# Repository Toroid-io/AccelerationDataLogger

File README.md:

# AccelerationDataLogger

**AccelerationDataLogger** provides a hardware-software bundle to
measure and log accelerations. Originally developed to measure
oscillations in engineering models, it may be used in the following
applications, among others:

 - Structural dynamics
 - Sports science
 - Simple vibration analysis
 - Fall detection
 - Wearables development
 - As an accelerometer playground

The board is capable of measuring **two accelerations simultaneously**
with a maximum sampling frequency of 800Hz, during 11 seconds. Longer
measurements are possible reducing the sampling rate, or using only one
accelerometer.

It currently uses jellybean parts as accelerometers. The board currently
supports the following breakout boards:
 - MPU6050 (GY-521 breakout)
 - ADXL345 (GY-291 and Sparkfun breakouts)

## Quick user manual
- Power the board using batteries or the USB cable.
- Fix the board into the structure or person.
- Calibrate the board by pressing the *Calibrate button*.
- Acquire the acceleration by pressing the *Acquire button*.
- Connect the board to your computer to download the data.

## The Hardware
You may find the KiCad schematic and board in the `Board` directory.

### Overview

The board does all the acquisition and storing procedure autonomously.
Hence, it may be battery powered during acquisition, and then connected
to a computer to download the data. In the current state, the board
requires at least 6.8V to work autonomously (this tension may be
provided by two LiPo cells or a 9V battery).

It has three pushable buttons, in order to reset the system, calibrate
the device and acquire data. A pushable switch enables or disables the
battery for autonomous mode.

The board may be connected to a computer using a USB micro-B cable.

That's all you need to know about the hardware!

### Memory

The board has 1MBit of RAM, where all the data is stored. Given that a
16-bit accelerometer provides 6 bytes of data for each measurement (plus
1 byte for the accelerometer ID), the board is capable of saving 18724
measurements.

That equals:
 - 11.7 seconds using two accelerometers at 800Hz
 - 23.4 seconds using one accelerometer at 800Hz
 - 6.24 minutes with one accelerometer at 50Hz
 - ...

## The Firmware

ChibiOS RTOS is used for the firmware. Tasks are used to separate the
acquisition of each sensor, write the RAM, and send measurements when
requested. Give a look into the `Firmware` folder.

## The acquisition software

A simple interface has been written in Qt C++, in order to download and
preview the data. The interface looks like this:

Currently, the interface only allows to connect and download the data
from the board. Future versions will allow the modification of some
parameters, such as the sampling frequency.

## I want one!

### Build One

You can build your own AccelerationDataLogger. Mounting the PCB requires
average soldering skills (0603 footprints and LQFP packages), but it is
the cheap way to go.

You can get the PCB from [OSH
Park](https://oshpark.com/shared_projects/0VAEaJ3K), or generate your
own Gerbers from the PCB. The BOM is in the `Board` directory.

### Get one built

We can send you a populated PCB. Just contact us at `admin [at]
toroid.io` for a quote.

## Development

### Contribute

Do you want to add or request a new feature? Did you find a bug in the
code? Create an issue or a pull request! All contributions are welcome.

### Future features

A non-exhaustive list of future features:
 - Add support to more accelerometers
 - Use a coin cell to power the system autonomously
 - Reduce the size of the board
 - Implement other MEMS features (DMP, fall detection)

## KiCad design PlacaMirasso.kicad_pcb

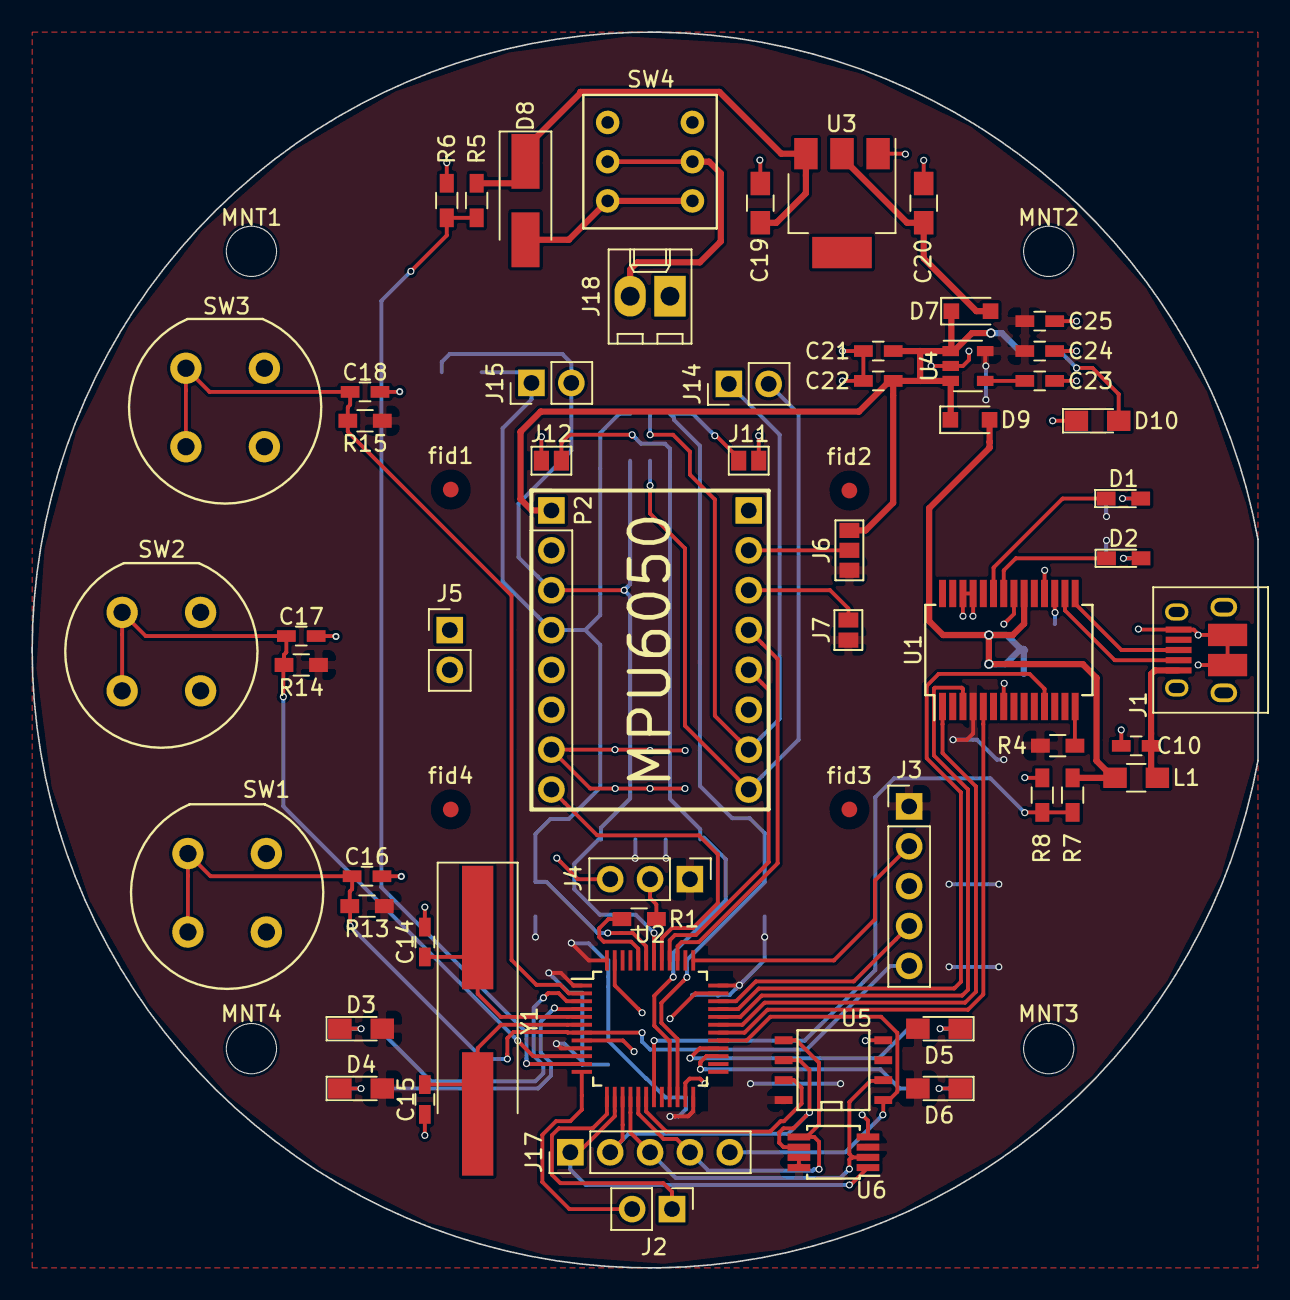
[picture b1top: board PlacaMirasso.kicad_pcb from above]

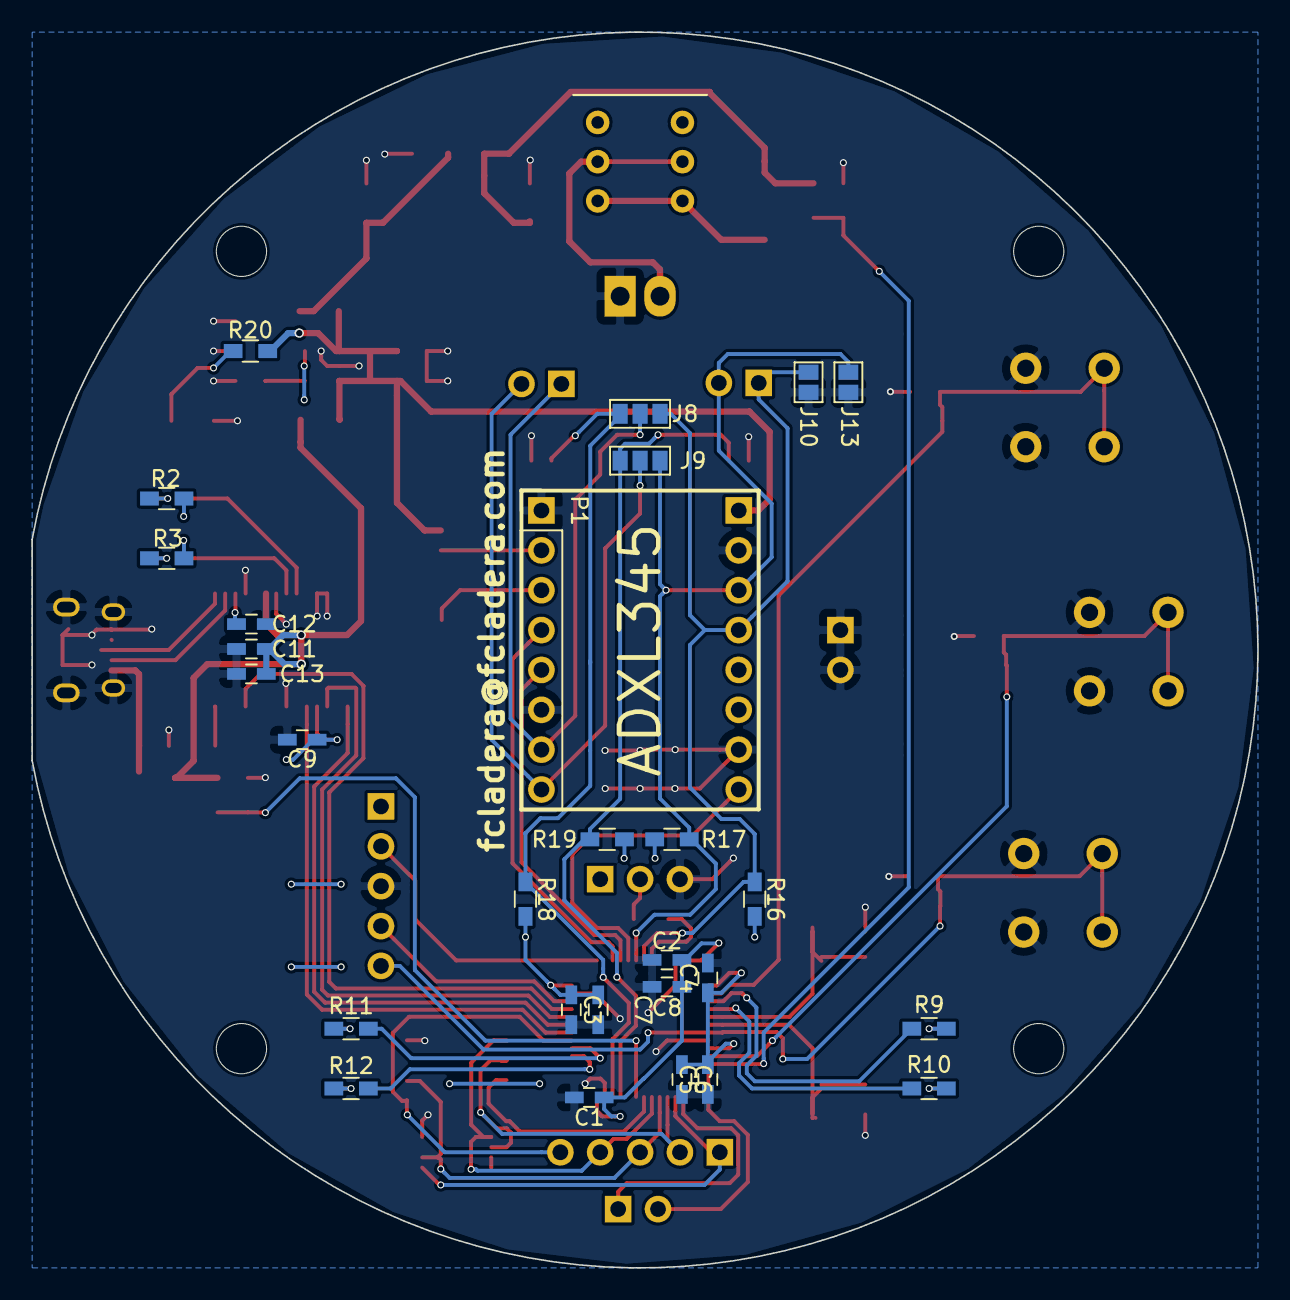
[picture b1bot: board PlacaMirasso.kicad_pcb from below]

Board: 2 copper layers, 78.1 x 78.7 mm, 94 parts (28 on the bottom side), 61 nets.

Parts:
C1, C2, C3, C4, C9, C11, C12, C16, C17, C18, C22, C25: 100nF; C_0603_HandSoldering
C5, C10, C23: 10nF_X7R; C_0603_HandSoldering
C6, C21, C24: 1uF_X5R; C_0603_HandSoldering
C7, C8, C13: 4.7uF; C_0603_HandSoldering
C14, C15: 10pF; C_0603_HandSoldering
C19, C20: 10uF; C_0805_HandSoldering
D1, D2: LED; LED_0603_HandSoldering
D3, D4, D5, D6, D10: LED; LED_0805_HandSoldering
D7, D9: BAT60JFILM; D_SOD-323_HandSoldering
D8: STPS2L30A; D_SMA_Handsoldering
J1: USB_OTG; USB_Micro-B_10103594-0001LF
J2: DEBUG; Pin_Header_Straight_1x02_Pitch2.54mm
J3: SWD; Pin_Header_Straight_1x05_Pitch2.54mm
J4: BOOT_JMP; Pin_Header_Straight_1x03_Pitch2.54mm
J5: GND; Pin_Header_Straight_1x02_Pitch2.54mm
J6, J8, J9: GS3
J7, J10, J11, J12, J13: GS2
J14: ANALIZER_ADXL; Pin_Header_Straight_1x02_Pitch2.54mm
J15: ANALIZER_MPU; Pin_Header_Straight_1x02_Pitch2.54mm
J17: SPI_ANALYZER; Pin_Header_Straight_1x05_Pitch2.54mm
J18: BAT; Molex_KK-6410-02_02x2.54mm_Straight
L1: MI0805K400R-10; L_0805_HandSoldering
MNT1, MNT2, MNT3, MNT4: MountHole; MountingHole_3.2mm_M3
P1: ADXL345; Pin_Header_Straight_1x08_Pitch2.54mm
P2: MPU_6050; Pin_Header_Straight_1x08_Pitch2.54mm
R1, R4, R6: 10k; R_0603_HandSoldering
R2, R3, R9, R10, R11, R12, R20: 1k1; R_0603_HandSoldering
R5, R8: 47k; R_0603_HandSoldering
R7: 39k; R_0603_HandSoldering
R13, R14, R15: 100k; R_0603_HandSoldering
R16, R17, R18, R19: 2k2; R_0603_HandSoldering
SW1, SW2, SW3: SW_Push_Dual; Push_E-Switch_KS01Q01
SW4: SW_DPDT_x2; Pushbutton-MHPS2283-DPDT
U1: FT232RL; SSOP-28_5.3x10.2mm_Pitch0.65mm
U2: STM32F072CBTx; LQFP-48_7x7mm_Pitch0.5mm
U3: LD1117S50TR; SOT-223
U4: LD3985M33R_SOT23; SOT-23-5
U5: 23LCRAM; SOIC-8-N
U6: 25LC_EEPROM; MSOP-8_3x3mm_Pitch0.65mm
Y1: 9C-8.000MBBK-T; Crystal_SMD_HC49-SD_HandSoldering
fid1, fid2, fid3, fid4: fiducial; Fiducial_1mm_Dia_2.54mm_Outer_CopperTop

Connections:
+3V3: C1.1, C2.1, C3.1, C4.1, C5.1, C6.1, C7.1, C8.1, C9.1, C24.1, C25.1, D3.2, D4.2, D5.2, D6.2, J3.1, J4.1, J6.1, J7.1, R2.1, R3.1, R4.1, R13.1, R14.1, R15.1, R16.2, R17.2, R18.2, R19.2, U1.4, U2.1, U2.9, U2.24, U2.36, U2.48, U4.5, U5.8, U6.3, U6.7, U6.8
+5V: C21.1, C22.1, D7.1, D9.1, J6.3, P2.1, R20.1, U4.1, U4.3
/BOOT_0: J4.2, R1.2
/CS_ADXL: J7.2, P1.3
/CTS_uC: U1.3, U2.32
/DEBUG_RX_uC: J2.1, U2.13
/DEBUG_TX_uC: J2.2, U2.12
/E5V: C20.1, D7.2, U3.2
/I2C1_SCL: J9.1, J13.1, J15.2, P2.3, R17.1, U2.42
/I2C1_SDA: J8.1, J10.1, J15.1, P2.4, R16.1, U2.43
/I2C2_SCL: J9.3, J12.1, R19.1, U2.21
/I2C2_SDA: J8.3, J11.1, R18.1, U2.22
/INT1_ADXL: P1.4, U2.39
/INT2_ADXL: P1.5, U2.40
/INT_MPU: P2.8, U2.41
/LED_1: R9.2, U2.3
/LED_2: R10.2, U2.4
/LED_3: R11.2, U2.28
/LED_4: R12.2, U2.27
/RESET: C16.1, J3.5, R13.2, SW1.2, SW1.4, U2.7
/RTS_uC: U1.11, U2.33
/Rx_uC: U1.1, U2.31
/SCL_ADXL: J9.2, J14.2, P1.8
/SDA_ADXL: J8.2, J14.1, P1.7
/SPI1_CS_1: J17.1, U2.14, U6.1
/SPI1_CS_2: J17.5, U2.29, U5.1
/SPI1_HOLD: U2.18, U5.7
/SPI1_MISO: J17.3, U2.16, U5.2, U6.2
/SPI1_MOSI: J17.4, U2.17, U5.5, U6.5
/SPI1_SCK: J17.2, U2.15, U5.6, U6.6
/SWCLK: J3.2, U2.37
/SWDIO: J3.4, U2.34
/Tx_uC: U1.5, U2.30
/U5V: C11.1, C13.1, D9.2, L1.1, R7.1, U1.20
/USR_BTN_1: C17.1, R14.2, SW2.2, SW2.4, U2.10
/USR_BTN_2: C18.1, R15.2, SW3.2, SW3.4, U2.2
/VBAT_ADC: R5.2, R6.1, U2.11
/VCC_ADXL: J6.2, P1.2
/VIN: C19.1, D8.1, R5.1, U3.3
/VUSB_ADC: R7.2, R8.1, U2.19
GND: C1.2, C2.2, C3.2, C4.2, C5.2, C6.2, C7.2, C8.2, C9.2, C10.2, C11.2, C12.2, C13.2, C14.2, C15.2, C16.2, C17.2, C18.2, C19.2, C20.2, C21.2, C22.2, C23.2, C24.2, C25.2, D10.1, J1.5, J1.6, J3.3, J4.3, J5.1, J5.2, J10.2, J11.2, J12.2, J13.2, J18.1, P1.1, P1.6, P2.2, P2.7, R6.2, R8.2, SW1.1, SW1.3, SW2.1, SW2.3, SW3.1, SW3.3, U1.7, U1.18, U1.21, U1.25, U1.26, U2.8, U2.23, U2.35, U2.47, U3.1, U4.2, U5.4, U6.4
unnamed: C10.1, J1.1, L1.2
unnamed: C12.1, U1.17
unnamed: C14.1, U2.5, Y1.1
unnamed: C15.1, U2.6, Y1.2
unnamed: C23.1, U4.4
unnamed: D1.1, U1.23
unnamed: D1.2, R2.2
unnamed: D2.1, U1.22
unnamed: D2.2, R3.2
unnamed: D3.1, R9.1
unnamed: D4.1, R10.1
unnamed: D5.1, R11.1
unnamed: D6.1, R12.1
unnamed: D8.2, SW4.3, SW4.6
unnamed: D10.2, R20.2
unnamed: J1.2, U1.16
unnamed: J1.3, U1.15
unnamed: J18.2, SW4.2, SW4.5
unnamed: R1.1, U2.44
unnamed: R4.2, U1.14

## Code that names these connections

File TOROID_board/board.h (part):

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/*
 * IO lines assignments.
 */
#define LED_1                 PAL_LINE(GPIOC, 14U)
#define LINE_SWDIO                  PAL_LINE(GPIOA, 13U)
#define LINE_SWCLK                  PAL_LINE(GPIOA, 14U)

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/*
 * GPIOA setup:
 *
 * PA0  - USR_BTN_1                 (input floating).
 * PA1  - VBAT_ADC                  (?).
 * PA2  - DEBUG_TX                  (alternate 1).
 * PA3  - DEBUG_RX                  (alternate 1).
 * PA4  - SPI_CS_1                  (output pushpull high).
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 * GPIOB setup:
 *
 * PB0  - SPI_HOLD                  (output pushpull high).
 * PB1  - VUSB_ADC                  (?).
 * PB2  - PIN2_NOT_USED             (input pullup).
 * PB3  - INT1_ADXL                 (input pullup).
 * PB4  - INT2_ADXL                 (input pullup).
 * PB5  - INT_MPU                   (input pullup).
 * PB6  - I2C1_SCL                  (output pullup - alternate 1).
 * PB7  - I2C1_SDA                  (input floating - alternate 1).
 * PB8  - PIN8_NOT_USED             (input pullup).
 * PB9  - PIN9_NOT_USED             (input pullup).
 * PB10 - I2C2_SCL                  (output pullup - alternate 1).
 * PB11 - I2C2_SDA                  (input floating - alternate 1).
 * PB12 - PIN12_NOT_USED            (input pullup).
 * PB13 - PIN13_NOT_USED            (input pullup).
 * PB14 - LED_4                     (output opendrain pullup).
 * PB15 - LED_3                     (output opendrain pullup).
 */
#define VAL_GPIOB_MODER             (PIN_MODE_OUTPUT(GPIOB_SPI_HOLD) |           \
                                     PIN_MODE_INPUT(GPIOB_VUSB_ADC) |           \
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 * PC10 - PIN10_NOT_USED            (input pullup).
 * PC11 - PIN11_NOT_USED            (input pullup).
 * PC12 - PIN12_NOT_USED            (input pullup).
 * PC13 - USR_BTN_2                 (input floating).
 * PC14 - GPIOC_LED_1               (output opendrain pullup).
 * PC15 - GPIOC_LED_2               (output opendrain pullup).
 */
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
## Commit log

2017-12-05 Init repo
2017-12-05 [Qt] Add update port button. Still some layout issues.
2017-12-05 [Qt] Moved Qt .gitignore into Qt folder
2017-12-05 [Qt] Sensor name is now correct (MPU and ADXL instead of A and B)
2017-12-05 [Qt] First draft
2017-12-05 [Qt] Moved all Qt sources into Qt folder
2017-12-05 [Qt] Small errors with modal windows. Better console messages.
2017-12-05 [Qt] New binary format for target config. Save button CB.
2017-12-05 [Qt] Add labels to plots. Download progress bar. Offset values.
2017-12-05 [Qt] AboutMe window. Menu. No data downloaded QMessageBox.
2017-12-05 [Fw] First draft
2017-12-05 [Fw] Basic drivers for I2C peripherals
2017-12-05 [Fw] Workaround for STM32F1 buggy I2C
2017-12-05 [Fw] Basic working program for BluePill I2C
2017-12-05 [Fw] OpenOCD flash script
2017-12-05 [Fw] First draft writing to SPI
2017-12-05 [Fw] First working version, still some issues (oversampling ADXL?)
2017-12-05 [Fw] Changed for TOROID board
2017-12-05 [Fw] First draft with drivers
2017-12-05 [Fw] Fixed flashing with openocd
2017-12-05 [Fw] More changes for TOROID board
2017-12-05 [Fw] Updated to stable_17.6 ChibiOS version
2017-12-05 [Fw] Removed bit banged I2C mode
2017-12-05 [Fw] Send message if there is no data to download
2017-12-05 [Fw] Basic I2C (MPU not working)
2017-12-05 [Fw] Fixed I2C lib for STM32F0
2017-12-05 [Fw] Now using UART driver for UART 1 instead of SERIAL
2017-12-05 [Fw] Now using external clock
2017-12-05 [Fw] Working SPI RAM
2017-12-05 [Fw] I2C basic is now working!
2017-12-05 [Fw] Bugfix when acquisitionDelay is 0. Fixed LEDs.
2017-12-05 [Fw] Led 3 blinks during transmission
2017-12-05 [Fw] Static config is now stored and loaded from EEPROM
2017-12-05 [Fw] Small modifications when coupling board with Qt software
2017-12-05 [Fw] Small code improvements in main.c
2017-12-05 [Fw] Remaining pin configurations in TOROID board
2017-12-05 [Fw] ADC for battery level working
2017-12-05 [Fw] Working buttons (for calibration and acquisition)
2017-12-05 [Fw] Improved transmission using serial driver
2017-12-05 [Fw] Increased process and exception stack size
2017-12-05 [Fw] Transmission using serial driver (quite slow)
2017-12-05 [Fw] Better filtering of Serial events (detect keystroke)
2017-12-05 [Fw] Splitted source files into MEMS and EEPROM folders
2017-12-05 [Fw] ADC is now stopped if an error is detected
2017-12-05 [Fw] Default config in EEPROM is now a function
2017-12-05 [Fw] Use +-2g for acceleration range
2017-12-05 [Fw] moved all firmware source code into Firmware folder
2017-12-05 First schematic - accelerometer board
2017-12-05 [Bd] Second draft
2017-12-05 [Bd] First PCB draft
2017-12-05 [Bd] New MCU
2017-12-05 [Bd] Moved PCB into Board directory.
2017-12-06 [Qt] Add application example image
2017-12-06 First global README.md draft
2017-12-10 [Qt] increase timeout in serial read, solves Windows problem
2017-12-11 [Fw] systemConfig structure can be changed through UART with 'c' command
2017-12-11 [Qt] UI can now modify (some) board parameters
2017-12-11 [Fw] Firmware now supports sample rate changement
2017-12-11 [Fw] some aesthetic improvements
2017-12-12 [Fw] accelerometers supporting different filters
2017-12-12 [Fw] Accelerometers now have an exponential high pass filter. Vector notation for acceleration. volatile used for some config variables.
2017-12-12 [Qt] better UI management. filterType supported in UI.
2017-12-12 [Fw] simpler printSystemConfig function
2017-12-12 [Fw] each accelerometer supports different filters
2017-12-12 [Qt] different filters for each accelerometer
2017-12-12 [Fw] better handling of mutual exclusion and mutexes
2017-12-13 [Qt] fixed some spanish translation leftovers

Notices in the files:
TOROID_board/board.h:
ChibiOS - Copyright (C) 2006..2016 Giovanni Di Sirio
Licensed under the Apache License, Version 2.0 (the "License");
